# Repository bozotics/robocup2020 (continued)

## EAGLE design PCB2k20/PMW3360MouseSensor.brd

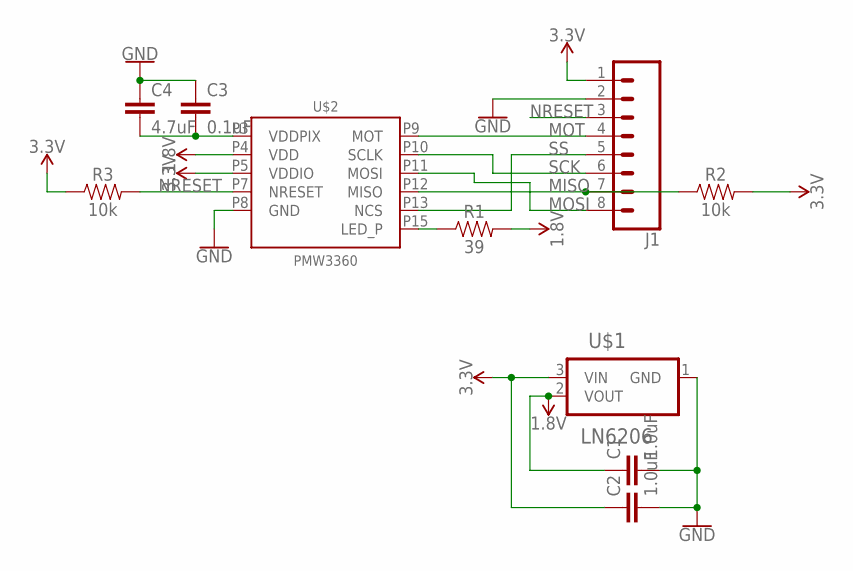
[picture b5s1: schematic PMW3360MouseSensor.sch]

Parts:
C1, C2: 1.0uF; 0603
C3: 0.1uF; 0603
C4: 4.7uF; 0603
J1: CONN_08LOCK; 1X08_LOCK
R1: 39; 0603
R2, R3: 10k; 0603
U$1: LN6206; SOT95P237X112-3N
U$2: PMW3360

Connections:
1.8V: C1.1, R1.2, U$1.2 (VOUT), U$2.P4 (VDD)
3.3V: C2.1, J1.1, R2.2, R3.1, U$1.3 (VIN), U$2.P5 (VDDIO)
GND: C1.2, C2.2, C3.1, C4.1, J1.2, U$1.1 (GND), U$2.P8 (GND)
MISO: J1.7, R2.1, U$2.P12 (MISO)
MOSI: J1.8, U$2.P11 (MOSI)
MOT: J1.4, U$2.P9 (MOT)
unnamed: R1.1, U$2.P15 (LED_P)
unnamed: C3.2, C4.2, U$2.P3 (VDDPIX)
NRESET: J1.3, R3.2, U$2.P7 (NRESET)
SCK: J1.6, U$2.P10 (SCLK)
SS: J1.5, U$2.P13 (NCS)

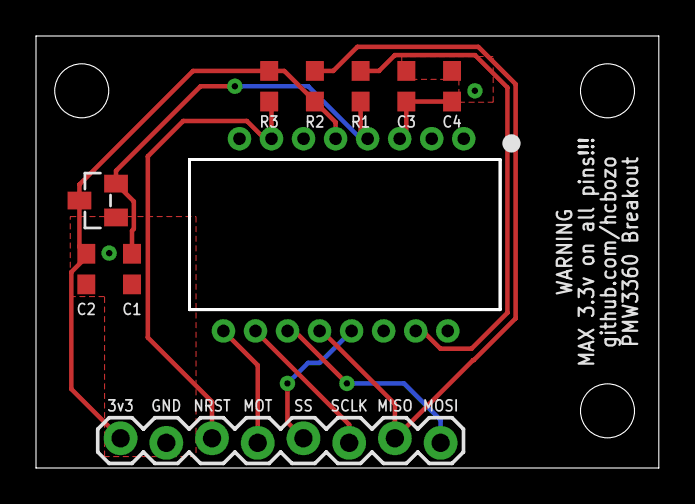
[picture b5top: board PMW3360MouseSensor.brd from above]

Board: 2 copper layers, 34.6 x 24.0 mm, 10 parts (0 on the bottom side), 11 nets.

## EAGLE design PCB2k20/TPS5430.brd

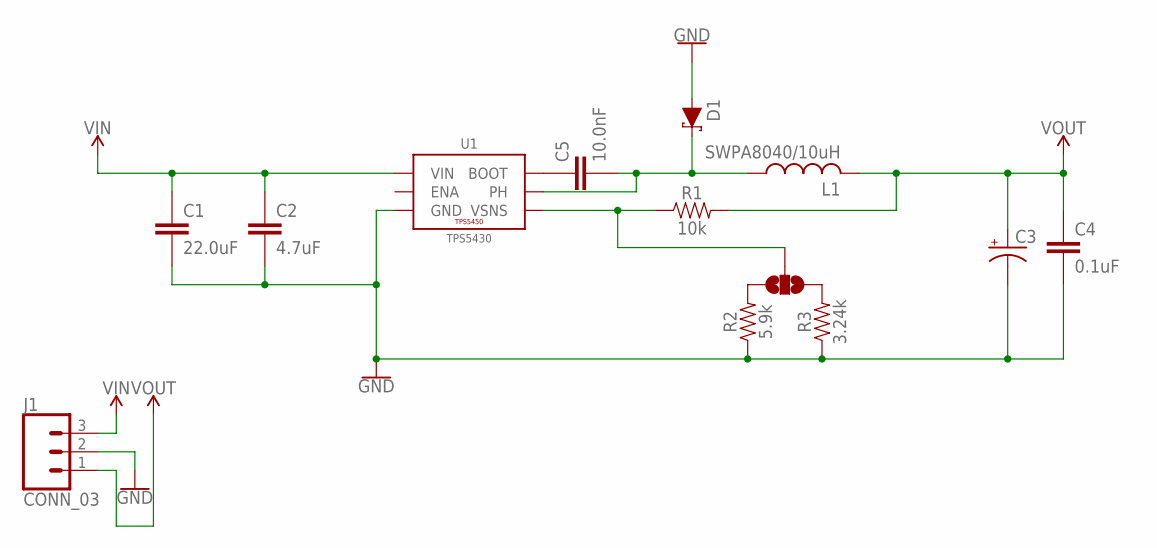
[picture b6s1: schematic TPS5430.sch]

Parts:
C1: 22.0uF; C1210
C2: 4.7uF; C0603
C3: 220uF; D/7343-31R
C4: 0.1uF; C0603
C5: 10.0nF; C0603
D1: 3A/40V/500mV; SMA-DIODE
J1: CONN_03; 1X03_LOCK
JP1: JUMPER-SMT_3_NO_NO-SILK; SMT-JUMPER_3_NO_NO-SILK
L1: SWPA8040/10uH; SWPA8040
R1: 10k; R0603
R2: 5.9k; R0603
R3: 3.24k; R0603
U1: TPS5430; POWERPAD-SOIC-8

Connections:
GND: C1.2, C2.2, C3.-, C4.2, D1.A, J1.2, R2.1, R3.1, U1.6 (GND), U1.9 (GND), U1.P$1 (GND), U1.P$2 (GND), U1.P$3 (GND), U1.P$4 (GND), U1.P$5 (GND), U1.P$6 (GND)
unnamed: JP1.2, R1.1, U1.4 (VSNS)
unnamed: C5.1, U1.1 (BOOT)
unnamed: JP1.3, R2.2
unnamed: JP1.1, R3.2
unnamed: C5.2, D1.C, L1.P1 (1), U1.8 (PH)
VIN: C1.1, C2.1, J1.3, U1.7 (VIN)
VOUT: C3.+, C4.1, J1.1, L1.P2 (2), R1.2

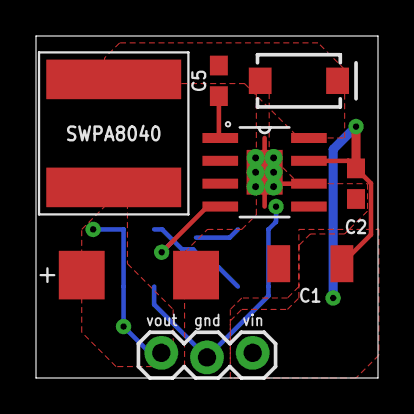
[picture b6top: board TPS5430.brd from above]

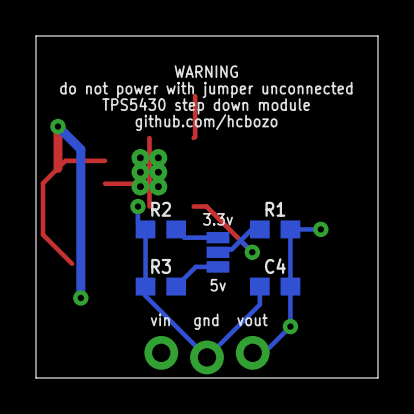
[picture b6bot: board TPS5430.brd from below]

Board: 2 copper layers, 19.0 x 19.0 mm, 13 parts (5 on the bottom side), 8 nets.

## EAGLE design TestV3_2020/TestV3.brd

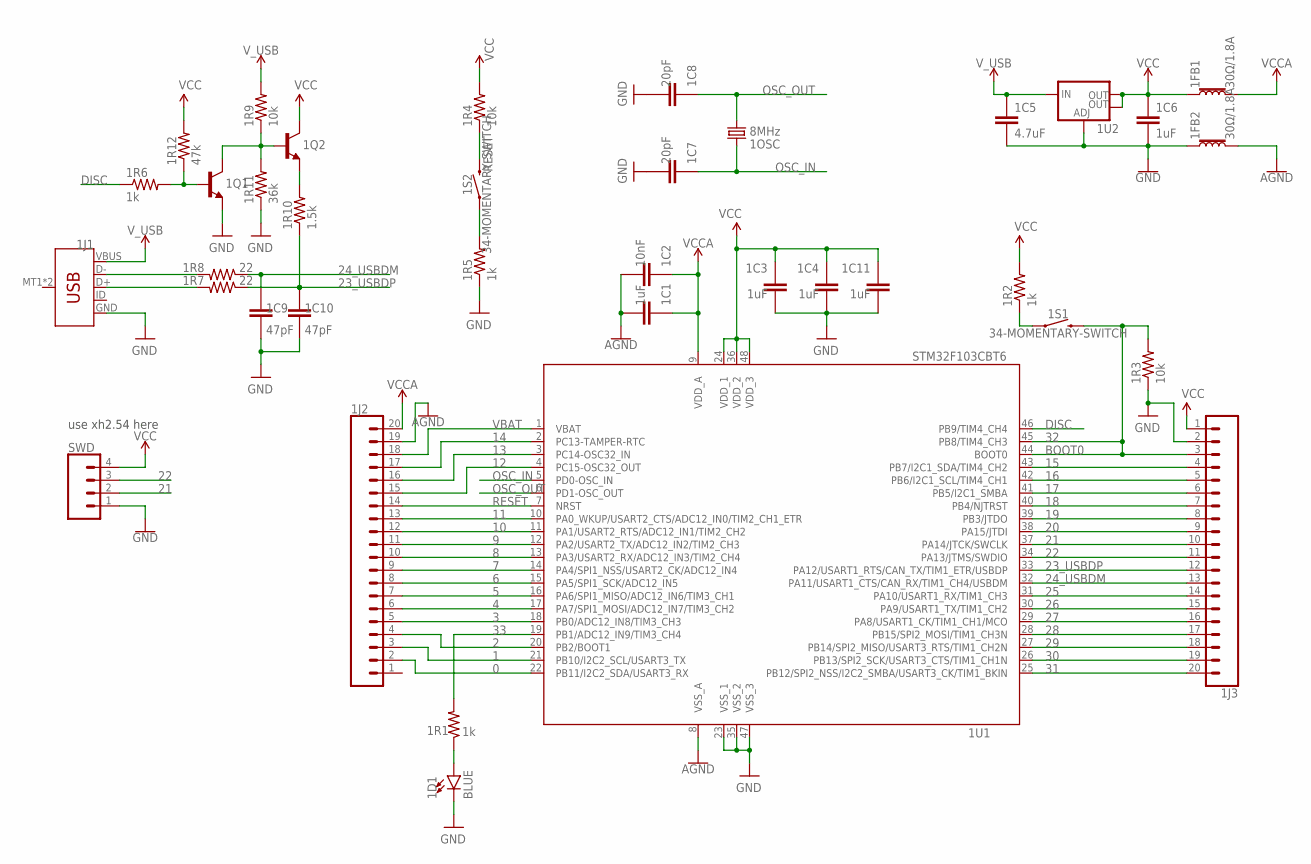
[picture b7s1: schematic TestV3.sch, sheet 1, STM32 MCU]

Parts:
1C1, 1C3, 1C4, 1C6, 1C11: 1uF; C0603
1C2: 10nF; C0603
1C5: 4.7uF; C0603
1C7, 1C8: 20pF; C0603
1C9, 1C10: 47pF; C0603
1D1: BLUE; LED-0603
1FB1, 1FB2: 30Ω/1.8A; 0603
1J1: USB-MICROB
1J2, 1J3: CONN_20LOCK; 1X20_LOCK
1OSC: 8MHz; CRYSTAL-SMD-5X3.2-2PAD
1Q1, 1Q2: 600mA/40V; SOT23-3
1R1, 1R2, 1R5, 1R6: 1k; R0603
1R3, 1R4, 1R9: 10k; R0603
1R7, 1R8: 22; R0603
1R10: 1.5k; R0603
1R11: 36k; R0603
1R12: 47k; R0603
1S1, 1S2: 34-MOMENTARY-SWITCH; 3*4-MOMENTARY-SWITCH
1U1: STM32F103CBT6; LQFP48
1U2: V_REG_LM1117SOT223; SOT223
SWD: CONN_04LOCK; 1X04_LOCK

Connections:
0: 1J2.2, 1U1.22 (PB11/I2C2_SDA/USART3_RX)
1: 1J2.3, 1U1.21 (PB10/I2C2_SCL/USART3_TX)
2: 1J2.4, 1U1.20 (PB2/BOOT1)
3: 1J2.5, 1U1.18 (PB0/ADC12_IN8/TIM3_CH3)
4: 1J2.6, 1U1.17 (PA7/SPI1_MOSI/ADC12_IN7/TIM3_CH2)
5: 1J2.7, 1U1.16 (PA6/SPI1_MISO/ADC12_IN6/TIM3_CH1)
6: 1J2.8, 1U1.15 (PA5/SPI1_SCK/ADC12_IN5)
7: 1J2.9, 1U1.14 (PA4/SPI1_NSS/USART2_CK/ADC12_IN4)
8: 1J2.10, 1U1.13 (PA3/USART2_RX/ADC12_IN3/TIM2_CH4)
9: 1J2.11, 1U1.12 (PA2/USART2_TX/ADC12_IN2/TIM2_CH3)
10: 1J2.12, 1U1.11 (PA1/USART2_RTS/ADC12_IN1/TIM2_CH2)
11: 1J2.13, 1U1.10 (PA0_WKUP/USART2_CTS/ADC12_IN0/TIM2_CH1_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)
12: 1J2.15, 1U1.4 (PC15-OSC32_OUT)
13: 1J2.16, 1U1.3 (PC14-OSC32_IN)
14: 1J2.17, 1U1.2 (PC13-TAMPER-RTC)
15: 1J3.4, 1U1.43 (PB7/I2C1_SDA/TIM4_CH2)
16: 1J3.5, 1U1.42 (PB6/I2C1_SCL/TIM4_CH1)
17: 1J3.6, 1U1.41 (PB5/I2C1_SMBA)
18: 1J3.7, 1U1.40 (PB4/NJTRST)
19: 1J3.8, 1U1.39 (PB3/JTDO)
20: 1J3.9, 1U1.38 (PA15/JTDI)
21: 1J3.10, 1U1.37 (PA14/JTCK/SWCLK), SWD.2
22: 1J3.11, 1U1.34 (PA13/JTMS/SWDIO), SWD.3
23_USBDP: 1C10.2, 1J3.12, 1R7.1, 1R10.1, 1U1.33 (PA12/USART1_RTS/CAN_TX/TIM1_ETR/USBDP)
24_USBDM: 1C9.2, 1J3.13, 1R8.1, 1U1.32 (PA11/USART1_CTS/CAN_RX/TIM1_CH4/USBDM)
25: 1J3.14, 1U1.31 (PA10/USART1_RX/TIM1_CH3)
26: 1J3.15, 1U1.30 (PA9/USART1_TX/TIM1_CH2)
27: 1J3.16, 1U1.29 (PA8/USART1_CK/TIM1_CH1/MCO)
28: 1J3.17, 1U1.28 (PB15/SPI2_MOSI/TIM1_CH3N)
29: 1J3.18, 1U1.27 (PB14/SPI2_MISO/USART3_RTS/TIM1_CH2N)
30: 1J3.19, 1U1.26 (PB13/SPI2_SCK/USART3_CTS/TIM1_CH1N)
31: 1J3.20, 1U1.25 (PB12/SPI2_NSS/I2C2_SMBA/USART3_CK/TIM1_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)
32: 1J3.3, 1R3.2, 1S1.P2 (2), 1U1.44 (BOOT0), 1U1.45 (PB8/TIM4_CH3)
33: 1R1.2, 1U1.19 (PB1/ADC12_IN9/TIM3_CH4)
AGND: 1C1.2, 1C2.2, 1FB2.2, 1J2.19, 1U1.8 (VSS_A)
DISC: 1R6.1, 1U1.46 (PB9/TIM4_CH4)
GND: 1C3.2, 1C4.2, 1C5.2, 1C6.2, 1C7.2, 1C8.2, 1C9.1, 1C10.1, 1C11.2, 1D1.C, 1FB2.1, 1J1.GND, 1J3.2, 1Q1.2 (E), 1R3.1, 1R5.1, 1R11.1, 1U1.23 (VSS_1), 1U1.35 (VSS_2), 1U1.47 (VSS_3), 1U2.1 (ADJ), SWD.1
unnamed: 1R2.1, 1S1.P1 (1)
unnamed: 1D1.A, 1R1.1
unnamed: 1R5.2, 1S2.P1 (1)
unnamed: 1Q2.2 (E), 1R10.2
unnamed: 1J1.D-, 1R8.2
unnamed: 1J1.D+, 1R7.2
unnamed: 1Q1.3 (C), 1Q2.1 (B), 1R9.1, 1R11.2
unnamed: 1Q1.1 (B), 1R6.2, 1R12.1
OSC_IN: 1C7.1, 1OSC.P$2 (2), 1U1.5 (PD0-OSC_IN)
OSC_OUT: 1C8.1, 1OSC.P$1 (1), 1U1.6 (PD1-OSC_OUT)
RESET: 1J2.14, 1R4.1, 1S2.P2 (2), 1U1.7 (NRST)
VBAT: 1J2.18, 1U1.1 (VBAT)
VCC: 1C3.1, 1C4.1, 1C6.1, 1C11.1, 1FB1.1, 1J3.1, 1Q2.3 (C), 1R2.2, 1R4.2, 1R12.2, 1U1.24 (VDD_1), 1U1.36 (VDD_2), 1U1.48 (VDD_3), 1U2.2 (OUT), 1U2.4 (OUT), SWD.4
VCCA: 1C1.1, 1C2.1, 1FB1.2, 1J2.20, 1U1.9 (VDD_A)
V_USB: 1C5.1, 1J1.VBUS, 1R9.2, 1U2.3 (IN)

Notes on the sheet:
BOOT0
use xh2.54 here

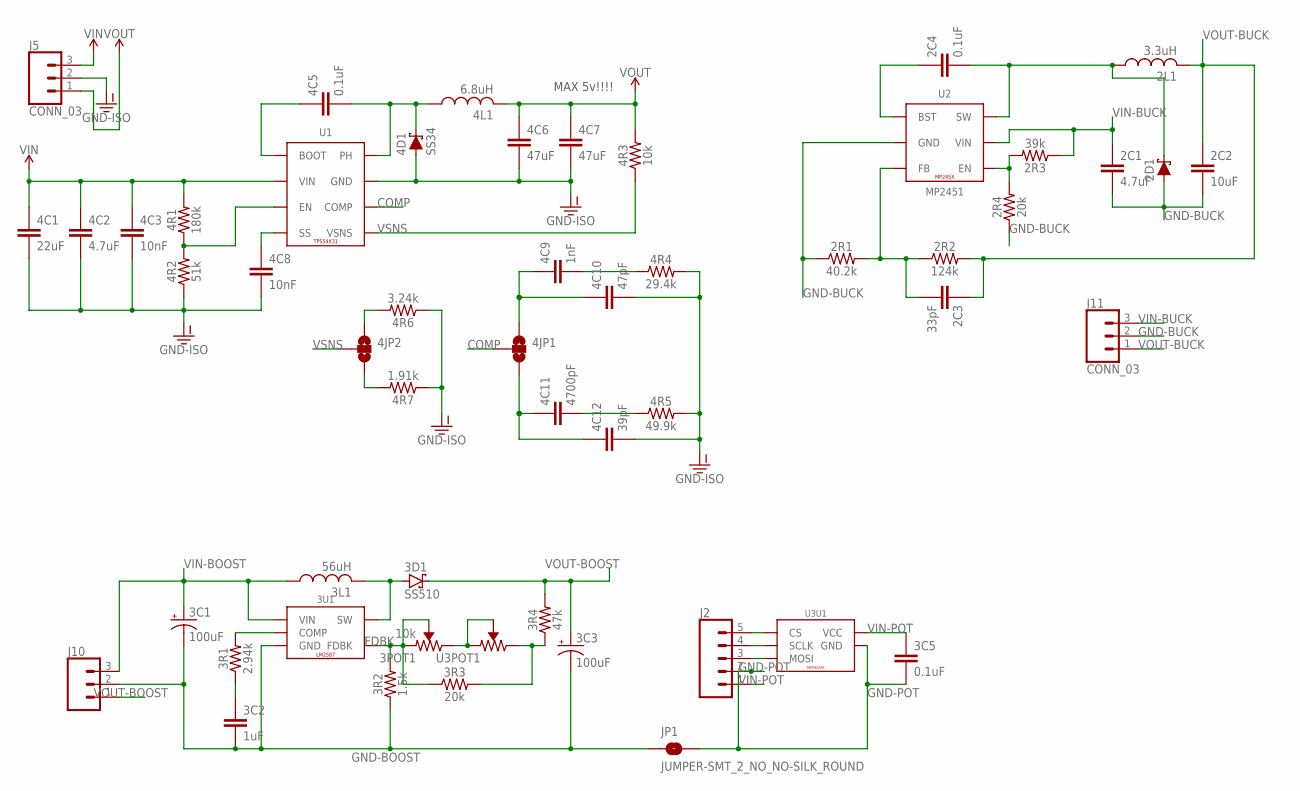
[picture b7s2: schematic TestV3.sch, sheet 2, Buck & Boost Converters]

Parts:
2C1, 4C2: 4.7uF; C0603
2C2: 10uF; C0603
2C3: 33pF; C0603
2C4, 3C5, 4C5: 0.1uF; C0603
2D1, 4D1: SS34; SMA-DIODE
2L1: 3.3uH; SWPA4030
2R1: 40.2k; R0603
2R2: 124k; R0603
2R3: 39k; R0603
2R4, 3R3: 20k; R0603
3C1: 100uF; PANASONIC_D
3C2: 1uF; C0603
3C3: 100uF; NIC_10X10.5_CAP
3D1: SS510; SMB
3L1: 56uH; CDRH127
3POT1: 10k; 3296-TRIMPOT
3R1: 2.94k; R0603
3R2: 1.5k; R0603
3R4: 47k; R0603
3U1: LM2587; TO-263
4C1: 22uF; C1210
4C3, 4C8: 10nF; C0603
4C6, 4C7: 47uF; C1206
4C9: 1nF; C0603
4C10: 47pF; C0603
4C11: 4700pF; C0603
4C12: 39pF; C0603
4JP1, 4JP2: JUMPER-SMT_3_NO_NO-SILK; SMT-JUMPER_3_NO_NO-SILK
4L1: 6.8uH; SWPA8040
4R1: 180k; R0603
4R2: 51k; R0603
4R3: 10k; R0603
4R4: 29.4k; R0603
4R5: 49.9k; R0603
4R6: 3.24k; R0603
4R7: 1.91k; R0603
J2: CONN_05LOCK; 1X05_LOCK
J5, J11: CONN_03; 1X03_LOCK
J10: CONN_03-SCREW-5MM; SCREWTERMINAL-5MM-3
JP1: JUMPER-SMT_2_NO_NO-SILK_ROUND; SMT-JUMPER_2_NO_NO-SILK_ROUND
U1: TPS54X31; POWERPAD-SOIC-8
U2: MP2451; SOT23-6-MP
U3: MCP41XXX; SOIC-8

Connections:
COMP: 4JP1.2, U1.6 (COMP)
FDBK: 3POT1.1 (CCW), 3POT1.2 (WIPER), 3R2.2, 3R3.1, 3U1.P2 (FDBK)
GND-BOOST: 3C1.-, 3C2.2, 3C3.-, 3R2.1, 3U1.P3 (GND), 3U1.P$1 (GND), 3U1.P$2 (GND), 3U1.P$3 (GND), 3U1.P$4 (GND), 3U1.P$5 (GND), 3U1.P$6 (GND), 3U1.P$7 (GND), 3U1.P$8 (GND), 3U1.P$9 (GND), 3U1.P$10 (GND), 3U1.P$11 (GND), 3U1.P$12 (GND), 3U1.P$13 (GND), 3U1.P$14 (GND), 3U1.P$15 (GND), 3U1.P$16 (GND), 3U1.P$17 (GND), 3U1.P$18 (GND), 3U1.P$19 (GND), 3U1.P$20 (GND), 3U1.TAB (GND), J10.2, JP1.1
GND-BUCK: 2C1.2, 2C2.2, 2D1.A, 2R1.1, 2R4.1, J11.2, U2.P2 (GND)
GND-ISO: 4C1.2, 4C2.2, 4C3.2, 4C6.2, 4C7.2, 4C8.2, 4C10.2, 4C12.2, 4D1.A, 4R2.1, 4R4.2, 4R5.2, 4R6.1, 4R7.1, J5.2, U1.7 (GND), U1.9 (GND), U1.P$1 (GND), U1.P$2 (GND), U1.P$3 (GND), U1.P$4 (GND), U1.P$5 (GND), U1.P$6 (GND)
GND-POT: 3C5.2, J2.2, JP1.2, U3.4 (GND)
unnamed: 2C3.2, 2R1.2, 2R2.1, U2.P3 (FB)
unnamed: 2C4.2, 2D1.C, 2L1.P1 (1), U2.P6 (SW)
unnamed: 2C4.1, U2.P1 (BST)
unnamed: 4C8.1, U1.4 (SS)
unnamed: 4C5.1, U1.1 (BOOT)
unnamed: 4C5.2, 4D1.C, 4L1.P1 (1), U1.8 (PH)
unnamed: 4R1.1, 4R2.2, U1.3 (EN)
unnamed: 4C9.2, 4R4.1
unnamed: 4C9.1, 4C10.1, 4JP1.1
unnamed: 3POT1.3 (CW), U3.5 (CCW), U3.6 (WIPER)
unnamed: 3R3.2, 3R4.1, U3.7 (CW)
unnamed: 2R3.2, 2R4.2, U2.P4 (EN)
unnamed: J2.3, U3.3 (MOSI)
unnamed: J2.4, U3.2 (SCLK)
unnamed: J2.5, U3.1 (CS)
unnamed: 3D1.A, 3L1.2, 3U1.P4 (SW)
unnamed: 3R1.2, 3U1.P1 (COMP)
unnamed: 3C2.1, 3R1.1
unnamed: 4C11.2, 4R5.1
unnamed: 4C11.1, 4C12.1, 4JP1.3
unnamed: 4JP2.1, 4R6.2
unnamed: 4JP2.3, 4R7.2
VIN: 4C1.1, 4C2.1, 4C3.1, 4R1.2, J5.3, U1.2 (VIN)
VIN-BOOST: 3C1.+, 3L1.1, 3U1.P5 (VIN), J10.3
VIN-BUCK: 2C1.1, 2R3.1, J11.3, U2.P5 (VIN)
VIN-POT: 3C5.1, J2.1, U3.8 (VCC)
VOUT: 4C6.1, 4C7.1, 4L1.P2 (2), 4R3.2, J5.1
VOUT-BOOST: 3C3.+, 3D1.C, 3R4.2, J10.1
VOUT-BUCK: 2C2.1, 2C3.1, 2L1.P2 (2), 2R2.2, J11.1
VSNS: 4JP2.2, 4R3.1, U1.5 (VSNS)

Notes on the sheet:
MAX 5v!!!!

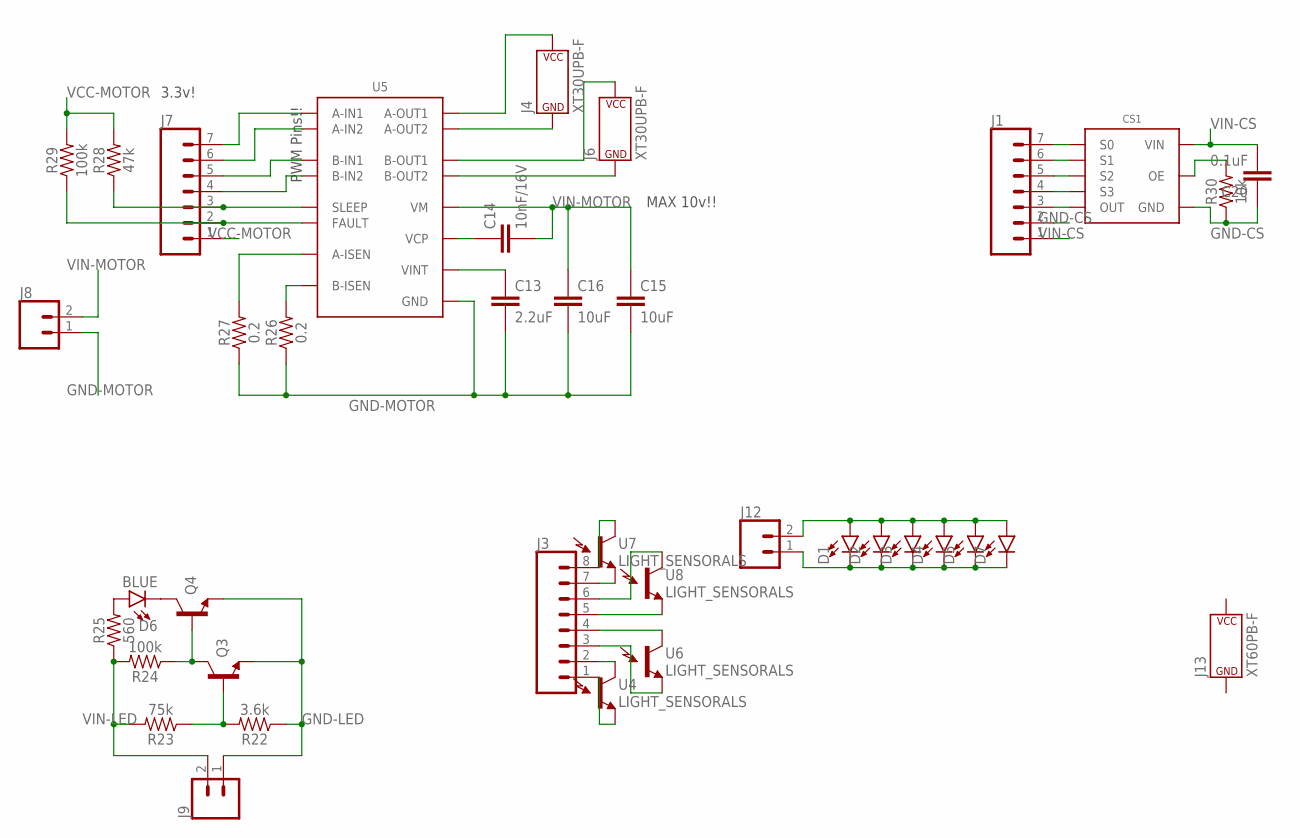
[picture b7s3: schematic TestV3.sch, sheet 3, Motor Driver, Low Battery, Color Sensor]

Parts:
C13: 2.2uF; C0603
C14: 10nF/16V; C0603
C15, C16: 10uF; C0805; VOLTAGE 16V
C20: 0.1uF; C0603
CS1: TCS3200; SOIC-8
D1, D2, D3, D4, D5, D7: 3528LED; 3528
D6: BLUE; LED-0603
J1, J7: CONN_07LOCK; 1X07_LOCK
J3: CONN_08LOCK; 1X08_LOCK
J4, J6: XT30UPB-F
J8: CONN_025MM; SCREWTERMINAL-5MM-2
J9, J12: CONN_02LOCK; 1X02_LOCK
J13: XT60PB-F
Q3, Q4: 600mA/40V; SOT23-3
R22: 3.6k; R0603
R23: 75k; R0603
R24, R29: 100k; R0603
R25: 560; R0603
R26, R27: 0.2; R0603
R28: 47k; R0603
R30: 10k; R0603
U4, U6, U7, U8: LIGHT_SENSORALS; ALS-PT19
U5: DRV8833; SSOP16

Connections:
GND-CS: C20.1, CS1.4 (GND), J1.2, R30.1
GND-LED: J9.1, Q3.2 (E), Q4.2 (E), R22.1
GND-MOTOR: C13.2, C15.2, C16.2, J8.1, R26.1, R27.1, U5.13 (GND), U5.PPAD (GND)
unnamed: D1.A, D2.A, D3.A, D4.A, D5.A, D7.A, J12.2
unnamed: D1.C, D2.C, D3.C, D4.C, D5.C, D7.C, J12.1
unnamed: J3.2, U4.C (C1)
unnamed: J3.1, U4.E (E1)
unnamed: J3.4, U6.C (C1)
unnamed: Q3.3 (C), Q4.1 (B), R24.1
unnamed: D6.A, R25.2
unnamed: D6.C, Q4.3 (C)
unnamed: J7.7, U5.16 (A-IN1)
unnamed: Q3.1 (B), R22.2, R23.1
unnamed: J7.6, U5.15 (A-IN2)
unnamed: J7.5, U5.9 (B-IN1)
unnamed: J7.4, U5.10 (B-IN2)
unnamed: J7.3, R28.1, U5.1 (SLEEP)
unnamed: J7.2, R29.1, U5.8 (FAULT)
unnamed: R26.2, U5.6 (B-ISEN)
unnamed: R27.2, U5.3 (A-ISEN)
unnamed: J4.+ (P$V+), U5.2 (A-OUT1)
unnamed: J4.- (P$V-), U5.4 (A-OUT2)
unnamed: J6.+ (P$V+), U5.7 (B-OUT1)
unnamed: J6.- (P$V-), U5.5 (B-OUT2)
unnamed: C14.1, U5.11 (VCP)
unnamed: C13.1, U5.14 (VINT)
unnamed: CS1.1 (S0), J1.7
unnamed: CS1.2 (S1), J1.6
unnamed: CS1.7 (S2), J1.5
unnamed: CS1.8 (S3), J1.4
unnamed: CS1.6 (OUT), J1.3
unnamed: CS1.3 (OE), R30.2
unnamed: J3.3, U6.E (E1)
unnamed: J3.8, U7.C (C1)
unnamed: J3.7, U7.E (E1)
unnamed: J3.5, U8.E (E1)
unnamed: J3.6, U8.C (C1)
VCC-MOTOR: J7.1, R28.2, R29.2
VIN-CS: C20.2, CS1.5 (VIN), J1.1
VIN-LED: J9.2, R23.2, R24.2, R25.1
VIN-MOTOR: C14.2, C15.1, C16.1, J8.2, U5.12 (VM)

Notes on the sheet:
PWM Pins!!
MAX 10v!!
3.3v!

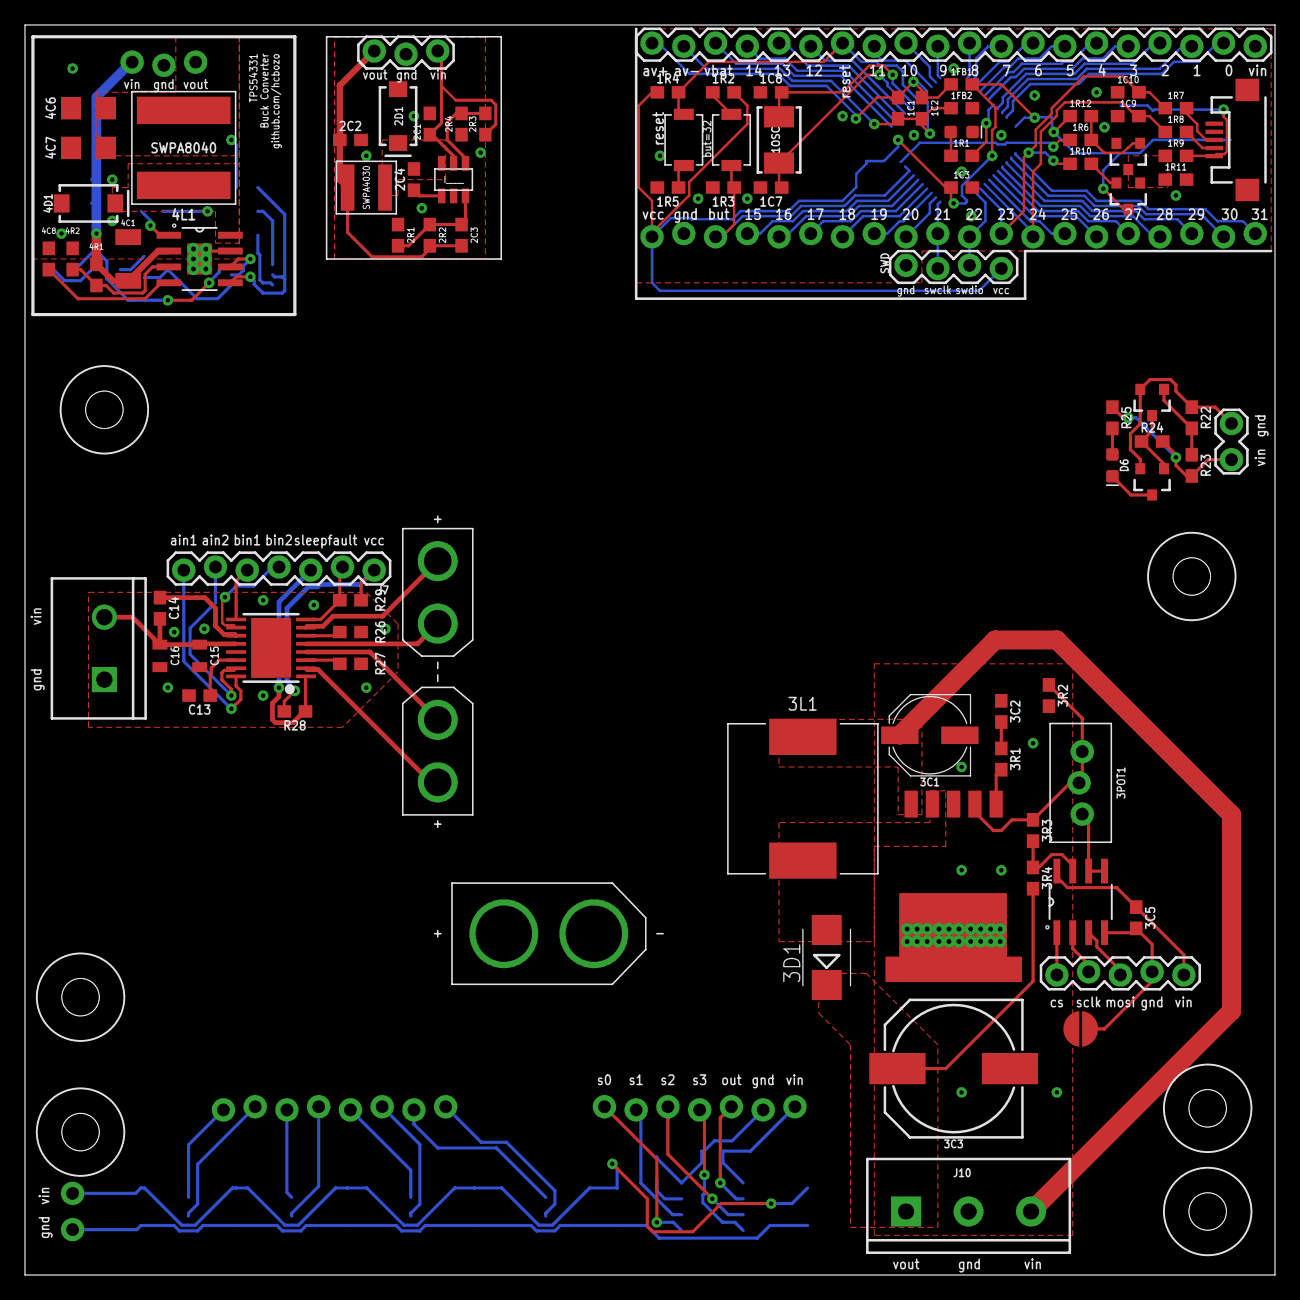
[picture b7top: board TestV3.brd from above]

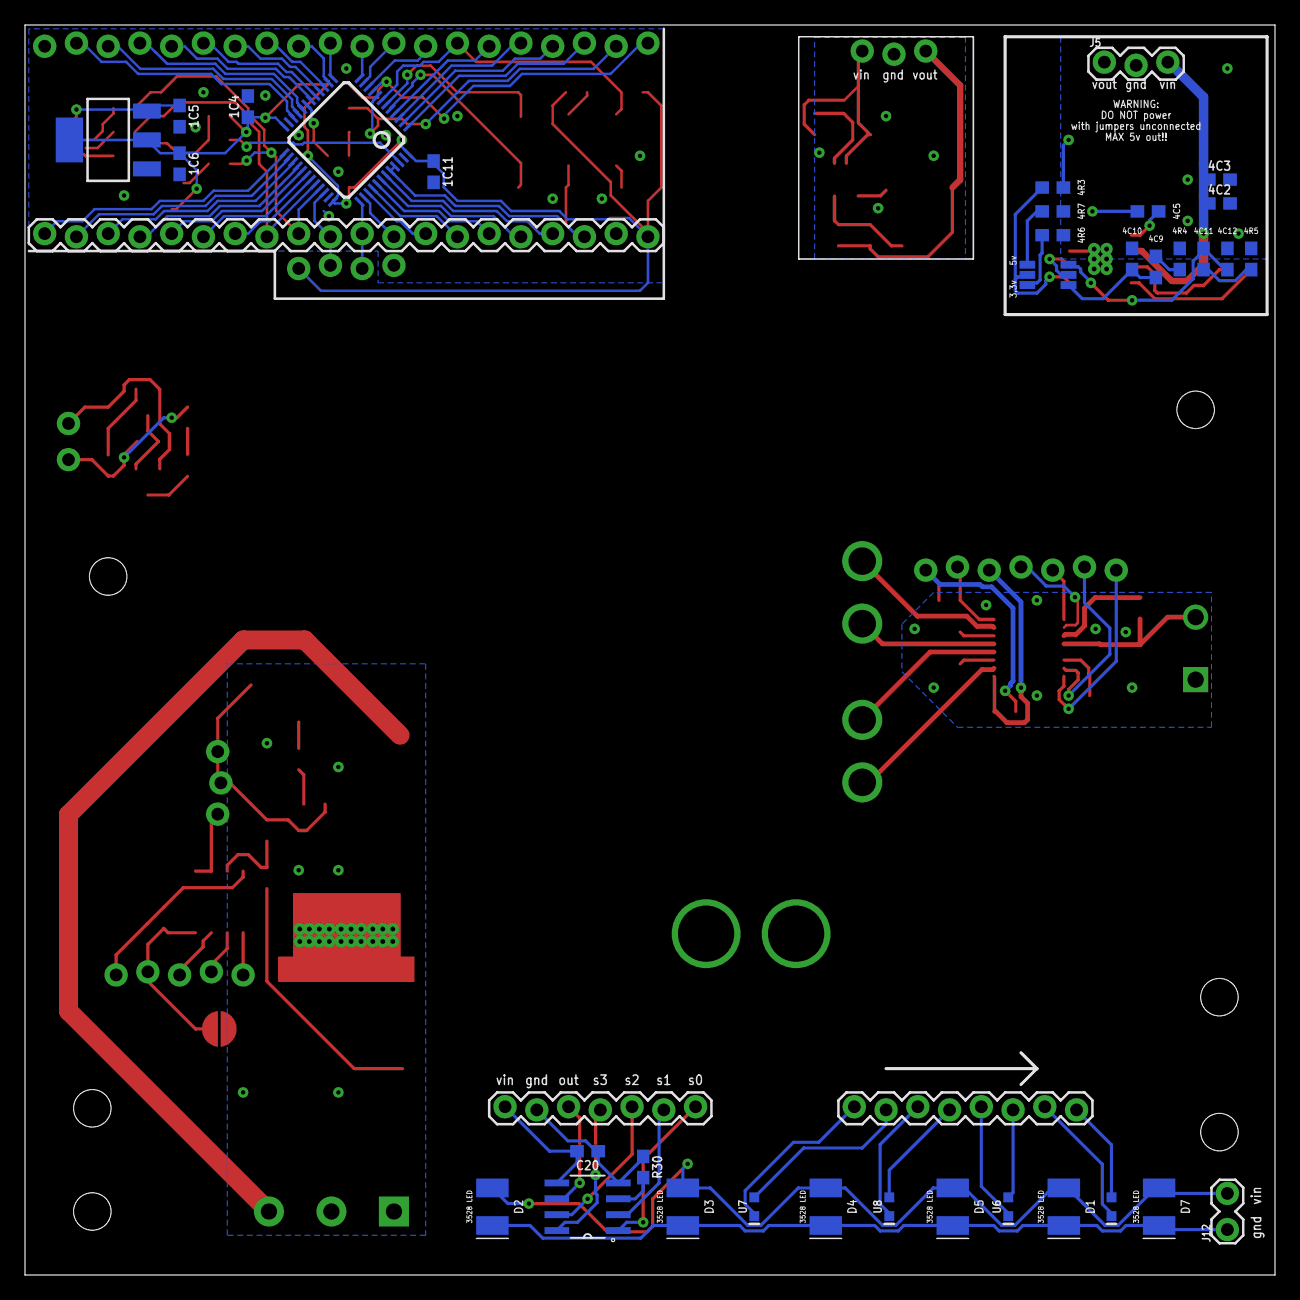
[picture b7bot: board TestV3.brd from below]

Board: 2 copper layers, 100.0 x 100.0 mm, 127 parts (38 on the bottom side), 129 nets.

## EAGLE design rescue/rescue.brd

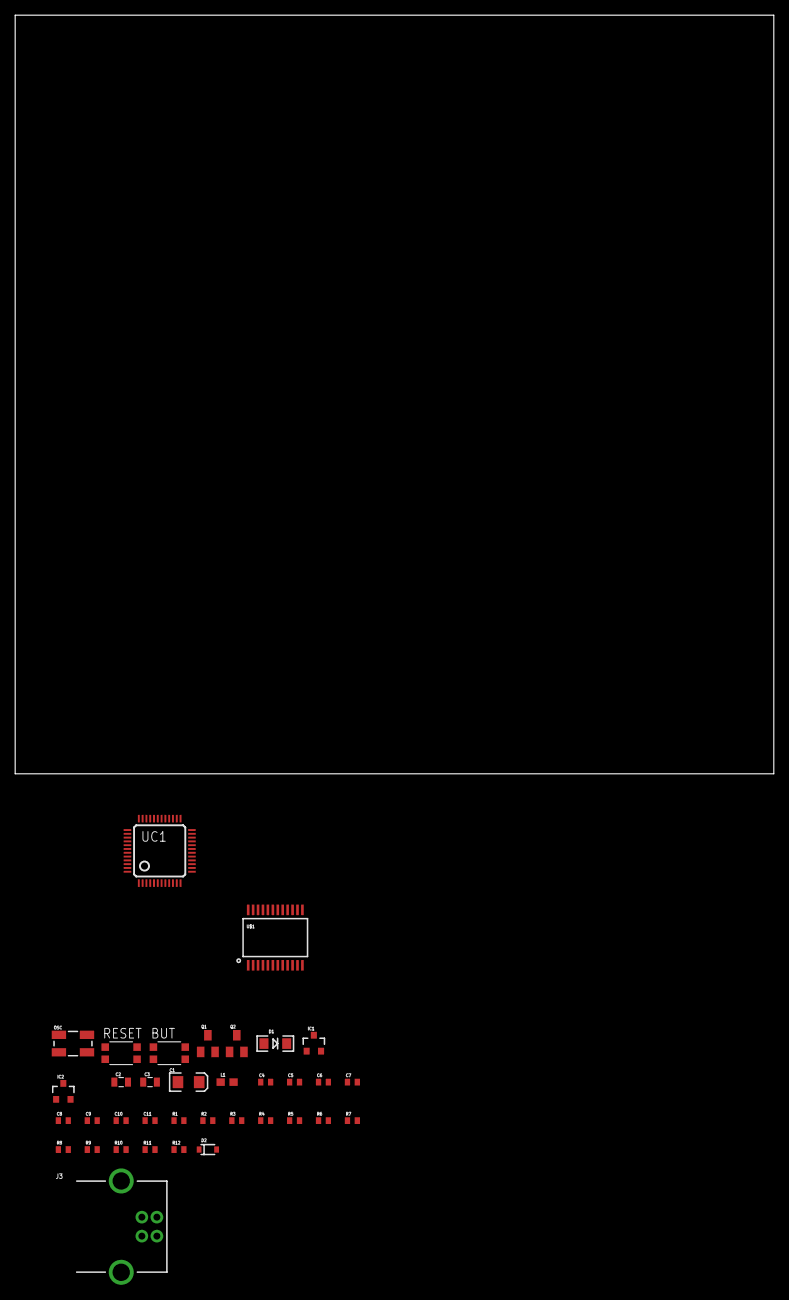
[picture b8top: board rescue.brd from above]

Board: 2 copper layers, 100.0 x 100.0 mm, 36 parts (0 on the bottom side), 22 nets, no tracks yet.

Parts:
BUT: KMR211GLFS; PUSHBUTTON-KMR241GLFS
C1: 100uF; EIA3216
C2, C3: 10uF; 0805
C4, C5, C6, C7: 1uF; C0402
C8, C9: 18pF; C0402
C10, C11: 47pF; C0402
D1: Blue; LED-1206
D2: SOD-323
IC1, IC2: MCP1703T-3302E/CB; SOT23
J3: USB_B_PTH; USB-B-PTH
L1: ferrite bead; 0603
OSC: 8MHz; CRYSTAL-SMD-5X3
Q1, Q2: NPN-BJT; SOT23
R1, R2, R4, R5: 1k; C0402
R3, R8, R9: 10k; C0402
R6, R7: 22; C0402
R10: 1.5k; C0402
R11: 36k; C0402
R12: 47k; C0402
RESET: KMR211GLFS; PUSHBUTTON-KMR241GLFS
U$1: TB6612FNG; SSOP24
UC1: STM32F103CBT6; LQFP48

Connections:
12V: C1.A, D2.1, IC1.3, IC2.3
23_USBDP: C11.2, R7.1, R10.1, UC1.33
24_USBDM: C10.2, R6.1, UC1.32
32: BUT.P$2, BUT.P$4, R9.2, UC1.44, UC1.45
33: R1.2, UC1.19
AV-: C3.2, C4.2, IC2.1, L1.1, UC1.8
DISC: R5.1, UC1.46
GND: C1.C, C2.2, C5.2, C6.2, C7.2, C8.2, C9.2, C10.1, C11.1, D1.C, IC1.1, J3.GND, L1.2, Q1.2, R4.1, R9.1, R11.1, UC1.23, UC1.35, UC1.47
unnamed: BUT.P$1, BUT.P$3, R2.1
unnamed: D1.A, R1.1
unnamed: R4.2, RESET.P$1, RESET.P$3
unnamed: Q2.2, R10.2
unnamed: J3.D-, R6.2
unnamed: J3.D+, R7.2
unnamed: Q1.3, Q2.1, R8.1, R11.2
unnamed: Q1.1, R5.2, R12.1
OSC_IN: C9.1, OSC.3, UC1.5
OSC_OUT: C8.1, OSC.1, UC1.6
RESET: R3.1, RESET.P$2, RESET.P$4, UC1.7
VCC: C2.1, C5.1, C6.1, C7.1, IC1.2, Q2.3, R2.2, R3.2, R12.2, UC1.24, UC1.36, UC1.48
VCCA: C3.1, C4.1, IC2.2, UC1.9
V_USB: D2.2, J3.VBUS, R8.2

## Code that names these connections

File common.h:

#include <HardwareSerial.h>
HardwareSerial Serial2(PA3, PA2);

//#define DEBUG

#define whitebot
//#define blackbot

#define ESC_1 PA8
#define ESC_2 PA1

#define XSHUT1 PC14
#define XSHUT2 PA5
#define XSHUT3 PB4
#define XSHUT4 PA15

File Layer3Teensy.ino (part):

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	DIP3.interval(50);
	DIP4.interval(50);

	pinMode(INM1, OUTPUT);
	pinMode(INM2, OUTPUT);
	pinMode(INM3, OUTPUT);
	pinMode(INM4, OUTPUT);
	digitalWriteFast(INM1, 0);
	digitalWriteFast(INM2, 1);
	digitalWriteFast(INM3, 1);
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
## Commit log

2019-11-25 reorganising and add test pcb
2019-11-26 minor change
2019-11-26 don't track eagle.epf files
2019-11-26 Finished schematic of buck converters will make changes to the values of compensation components to make them more standard values
2019-11-27 shift buck converters to own library rcl
2019-12-10 Added Datasheets folder and cleaned up the schematic to use less random libraries
2019-12-10 Small changes to STM32: Added protection diodes between V_USB and VCC, and added ferrite beads to filter analog voltage
2019-12-11 Don't track EAGLE backup files
2019-12-13 IDK what I did but added datasheet of INA20x current shunt controller cuz will be using that
2019-12-13 Rearranged datasheet folder and deleted unused ones Also added BD2244 Power Load Switch IC (For short circuit protection)
2019-12-13 Finally finished LM2587 Boost Circuit, together with INA169+LM393 overcurrent protection
2019-12-13 super annoying
2019-12-18 Add more datasheets and clean up
2019-12-18 Finished low battery detection, motor driver and TCS3200 color sensor.
2019-12-18 Finished TPS54331 Buck Converter Board Layout and Isolation Final Size ~2.2*2.2cm But I should probably add some test points and fix the silkscreen
2019-12-19 Added TCS3200 Datasheet and updated buck converter board layout fixed the silkscreen for buck converter and finalise design
2019-12-19 finished stm32 board layout, the end is near!
2019-12-20 MP2451 Buck Converter Circuit
2019-12-20 Fixed silkscreen for stm32 and mp2541
2019-12-20 finished all the board layouts
2019-12-20 added more light sensors and lights to test and optimise positioning, added xt60 for test fitting
2019-12-23 minor changes, mostly fixed the values of some components
2019-12-29 Mouse Sensor Socket because $10 sensors should be reused
2019-12-29 Make the screws not hit the lens
2020-01-21 Finalise PMW3360 breakout - done pin markings and cleanup - swapped position of some pins to route stuff more easily
2020-01-21 IR and ESC datasheets
2020-01-22 Start on layer 4: WS2812B and STM32
2020-01-27 Layer 4: linked with fusion so its easier to move stuff around
2020-01-27 add ws2812b rgb led datasheet
2020-01-28 TPS54331 didnt really work because china, so we are using the TPS5430 now..
2020-01-30 finish layer 4 and start on layer 3, TODO: silkscreen for layer4
2020-02-02 no idea what i did but need to save this so
2020-02-02 Layer 3 placement kinda done, routing to wait for layer 1 signals to be confirmed. also renamed some folders because windows explorer doesnt like the old name
2020-02-03 continue on layer 1 schematic, just need to finish this asap and quickly start positioning
2020-02-06 added a switch to choose between programmer power and battery power for STM32
2020-02-08 placement done wow that was difficult
2020-02-08 half routed
2020-02-10 done just need to silkscreen now!!!
2020-02-12 add gerbers, please everything turn out well!
2020-02-19 update values
2020-02-23 Change pullup resistor to value we alr have
2020-03-19 Welp I should go kms dumb mistakes time for Rescue PCB V2
2020-03-31 Initial
2020-03-31 Fixed intellisense issues
2020-04-01 Fix light calibration (Don't send the raw sensor values directly, calculate on Layer 1)
2020-04-02 derps
2020-04-02 Make serial not so annoying
2020-04-02 Motor switch initial testing
2020-04-30 don't use annoying color
2020-05-02 update cpptools config
2020-05-05 add ALS PT19 datasheet
2020-05-05 going pro
2020-05-06 cleanup
2020-05-06 add l3 IMU
2020-05-17 Use new intellisense gcc-arm mode
2020-05-17 change Arduino_Core_STM32 version
2020-05-17 don't use username, make it portable
2020-06-27 add PCB-3dModel branch
2020-06-27 add schematic PDFs
2020-06-27 hmmm... I'll move to a different repo
2020-06-27 move to new repo, fix links
2020-06-27 add README
2020-06-27 BROKEN VERSION for 3d models
2020-06-27 change repo name
2020-06-27 README: point non-broken PCB to new branch
2020-06-27 add inventhub
2020-06-27 [redacted] I was forced to make my messages SFW :(
2020-06-27 added bigfield
2020-07-05 whoops update PDFs to have all the sheets
2021-03-25 added movement, ball tracking, pi serial (all spaghetti code courtesy of me)
2021-03-25 control dribblers from serial
2021-03-25 added layer4 serial (basic dribbler control)
2021-04-19 make light threshold manually keyable to solve problem of stupid value dropping randomly
2021-04-19 short delay to set motor + turn off led
2021-04-22 changed way too much shit to record but committing this before completely changing serial code
2021-04-22 cleaned debug stuff + updated thresholds
2022-03-26 last update (will clean this up "one day")
